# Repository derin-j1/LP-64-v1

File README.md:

# LP-64-v1
Launchpad development board featuring a grid of identical input/output modules, organized trace routing, control circuitry on the right side, and interface connectors. Designed for prototyping, testing, and managing multiple channels within an embedded electronics system.

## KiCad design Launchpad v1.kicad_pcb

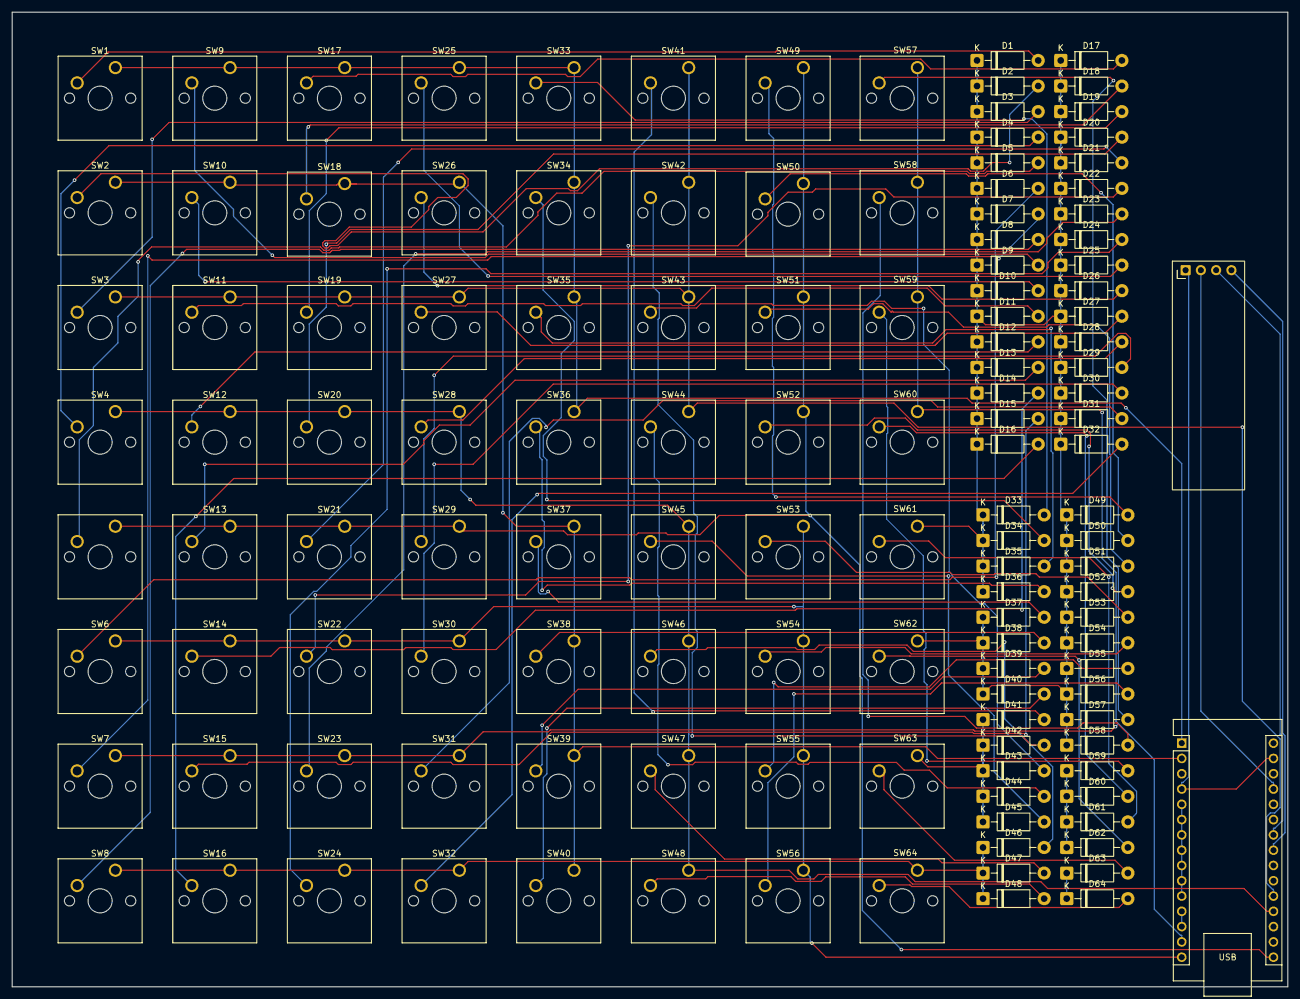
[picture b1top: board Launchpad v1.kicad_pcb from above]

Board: 2 copper layers, 211.9 x 161.9 mm, 130 parts (0 on the bottom side), 76 nets.

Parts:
A1: Arduino_Nano_Every; Arduino_Nano
D1, D2, D3, D4, D5, D6, D7, D8, D9, D10, D11, D12, D13, D14, D15, D16, D17, D18, D19, D20, D21, D22, D23, D24, D25, D26, D27, D28, D29, D30, D31, D32, D33, D34, D35, D36, D37, D38, D39, D40, D41, D42, D43, D44, D45, D46, D47, D48, D49, D50, D51, D52, D53, D54, D55, D56, D57, D58, D59, D60, D61, D62, D63, D64: 1N4001; D_DO-41_SOD81_P10.16mm_Horizontal
SW1, SW2, SW3, SW4, SW5, SW6, SW7, SW8, SW9, SW10, SW11, SW12, SW13, SW14, SW15, SW16, SW17, SW18, SW19, SW20, SW21, SW22, SW23, SW24, SW25, SW26, SW27, SW28, SW29, SW30, SW31, SW32, SW33, SW34, SW35, SW36, SW37, SW38, SW39, SW40, SW41, SW42, SW43, SW44, SW45, SW46, SW47, SW48, SW49, SW50, SW51, SW52, SW53, SW54, SW55, SW56, SW57, SW58, SW59, SW60, SW61, SW62, SW63, SW64: SW_Push_45deg; SW_Cherry_MX_1.00u_PCB
U1: OLED_0.91_128x32

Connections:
COL 1: A1.5 (D2), A1.6 (D3), A1.7 (D4), A1.8 (D5), A1.9 (D6), A1.10 (D7), A1.11 (D8), A1.12 (D9), A1.13 (D10), D1.1 (K), D2.1 (K), D3.1 (K), D4.1 (K), D5.1 (K), D6.1 (K), D7.1 (K), D8.1 (K), D9.1 (K), D10.1 (K), D11.1 (K), D12.1 (K), D13.1 (K), D14.1 (K), D15.1 (K), D16.1 (K), D17.1 (K), D18.1 (K), D19.1 (K), D20.1 (K), D21.1 (K), D22.1 (K), D23.1 (K), D24.1 (K), D25.1 (K), D26.1 (K), D27.1 (K), D28.1 (K), D29.1 (K), D30.1 (K), D31.1 (K), D32.1 (K), D33.1 (K), D34.1 (K), D35.1 (K), D36.1 (K), D37.1 (K), D38.1 (K), D39.1 (K), D40.1 (K), D41.1 (K), D42.1 (K), D43.1 (K), D44.1 (K), D45.1 (K), D46.1 (K), D47.1 (K), D48.1 (K), D49.1 (K), D50.1 (K), D51.1 (K), D52.1 (K), D53.1 (K), D54.1 (K), D55.1 (K), D56.1 (K), D57.1 (K), D58.1 (K), D59.1 (K), D60.1 (K), D61.1 (K), D62.1 (K), D63.1 (K), D64.1 (K), SW8.1, SW16.1, SW24.1, SW32.1, SW61.1, SW62.1, SW63.1, SW64.1
COL 2: A1.14 (MOSI), SW7.1, SW15.1, SW23.1, SW31.1, SW57.1, SW58.1, SW59.1, SW60.1
COL 3: A1.15 (MISO), SW6.1, SW14.1, SW22.1, SW30.1, SW53.1, SW54.1, SW55.1, SW56.1
COL 4: A1.16 (SCK), SW5.1, SW13.1, SW21.1, SW29.1, SW49.1, SW50.1, SW51.1, SW52.1
COL 5: A1.19 (A0), SW4.1, SW12.1, SW20.1, SW28.1, SW45.1, SW46.1, SW47.1, SW48.1
COL 6: A1.20 (A1), SW3.1, SW11.1, SW19.1, SW27.1, SW41.1, SW42.1, SW43.1, SW44.1
COL 7: A1.2 (RX1), SW2.1, SW10.1, SW18.1, SW26.1, SW37.1, SW38.1, SW39.1, SW40.1
COL 8: A1.1 (TX1), SW1.1, SW9.1, SW17.1, SW25.1, SW33.1, SW34.1, SW35.1, SW36.1
GND: A1.4 (GND), A1.29 (GND), U1.1 (GND)
unnamed: A1.27 (+5V), U1.2 (VCC)
unnamed: D1.2 (A), SW1.2
unnamed: D2.2 (A), SW2.2
unnamed: D3.2 (A), SW3.2
unnamed: D4.2 (A), SW4.2
unnamed: D5.2 (A), SW5.2
unnamed: D6.2 (A), SW6.2
unnamed: D7.2 (A), SW7.2
unnamed: D8.2 (A), SW8.2
unnamed: D9.2 (A), SW9.2
unnamed: D10.2 (A), SW10.2
unnamed: D11.2 (A), SW11.2
unnamed: D12.2 (A), SW12.2
unnamed: D13.2 (A), SW13.2
unnamed: D14.2 (A), SW14.2
unnamed: D15.2 (A), SW15.2
unnamed: D16.2 (A), SW16.2
unnamed: D17.2 (A), SW17.2
unnamed: D18.2 (A), SW18.2
unnamed: D19.2 (A), SW19.2
unnamed: D20.2 (A), SW20.2
unnamed: D21.2 (A), SW21.2
unnamed: D22.2 (A), SW22.2
unnamed: D23.2 (A), SW23.2
unnamed: D24.2 (A), SW24.2
unnamed: D25.2 (A), SW25.2
unnamed: D26.2 (A), SW26.2
unnamed: D27.2 (A), SW27.2
unnamed: D28.2 (A), SW28.2
unnamed: D29.2 (A), SW29.2
unnamed: D30.2 (A), SW30.2
unnamed: D31.2 (A), SW31.2
unnamed: D32.2 (A), SW32.2
unnamed: D33.2 (A), SW33.2
unnamed: D34.2 (A), SW34.2
unnamed: D35.2 (A), SW35.2
unnamed: D36.2 (A), SW36.2
unnamed: D37.2 (A), SW37.2
unnamed: D38.2 (A), SW38.2
unnamed: D39.2 (A), SW39.2
unnamed: D40.2 (A), SW40.2
unnamed: D41.2 (A), SW41.2
unnamed: D42.2 (A), SW42.2
unnamed: D43.2 (A), SW43.2
unnamed: D44.2 (A), SW44.2
unnamed: D45.2 (A), SW45.2
unnamed: D46.2 (A), SW46.2
unnamed: D47.2 (A), SW47.2
unnamed: D48.2 (A), SW48.2
unnamed: D49.2 (A), SW49.2
unnamed: D50.2 (A), SW50.2
unnamed: D51.2 (A), SW51.2
unnamed: D52.2 (A), SW52.2
unnamed: D53.2 (A), SW53.2
unnamed: D54.2 (A), SW54.2
unnamed: D55.2 (A), SW55.2
unnamed: D56.2 (A), SW56.2
unnamed: D57.2 (A), SW57.2
unnamed: D58.2 (A), SW58.2
unnamed: D59.2 (A), SW59.2
unnamed: D60.2 (A), SW60.2
unnamed: D61.2 (A), SW61.2
unnamed: D62.2 (A), SW62.2
unnamed: D63.2 (A), SW63.2
unnamed: D64.2 (A), SW64.2
SCL: A1.24 (SCL/A5), U1.3 (SCL)
SDA: A1.23 (SDA/A4), U1.4 (SDA)
